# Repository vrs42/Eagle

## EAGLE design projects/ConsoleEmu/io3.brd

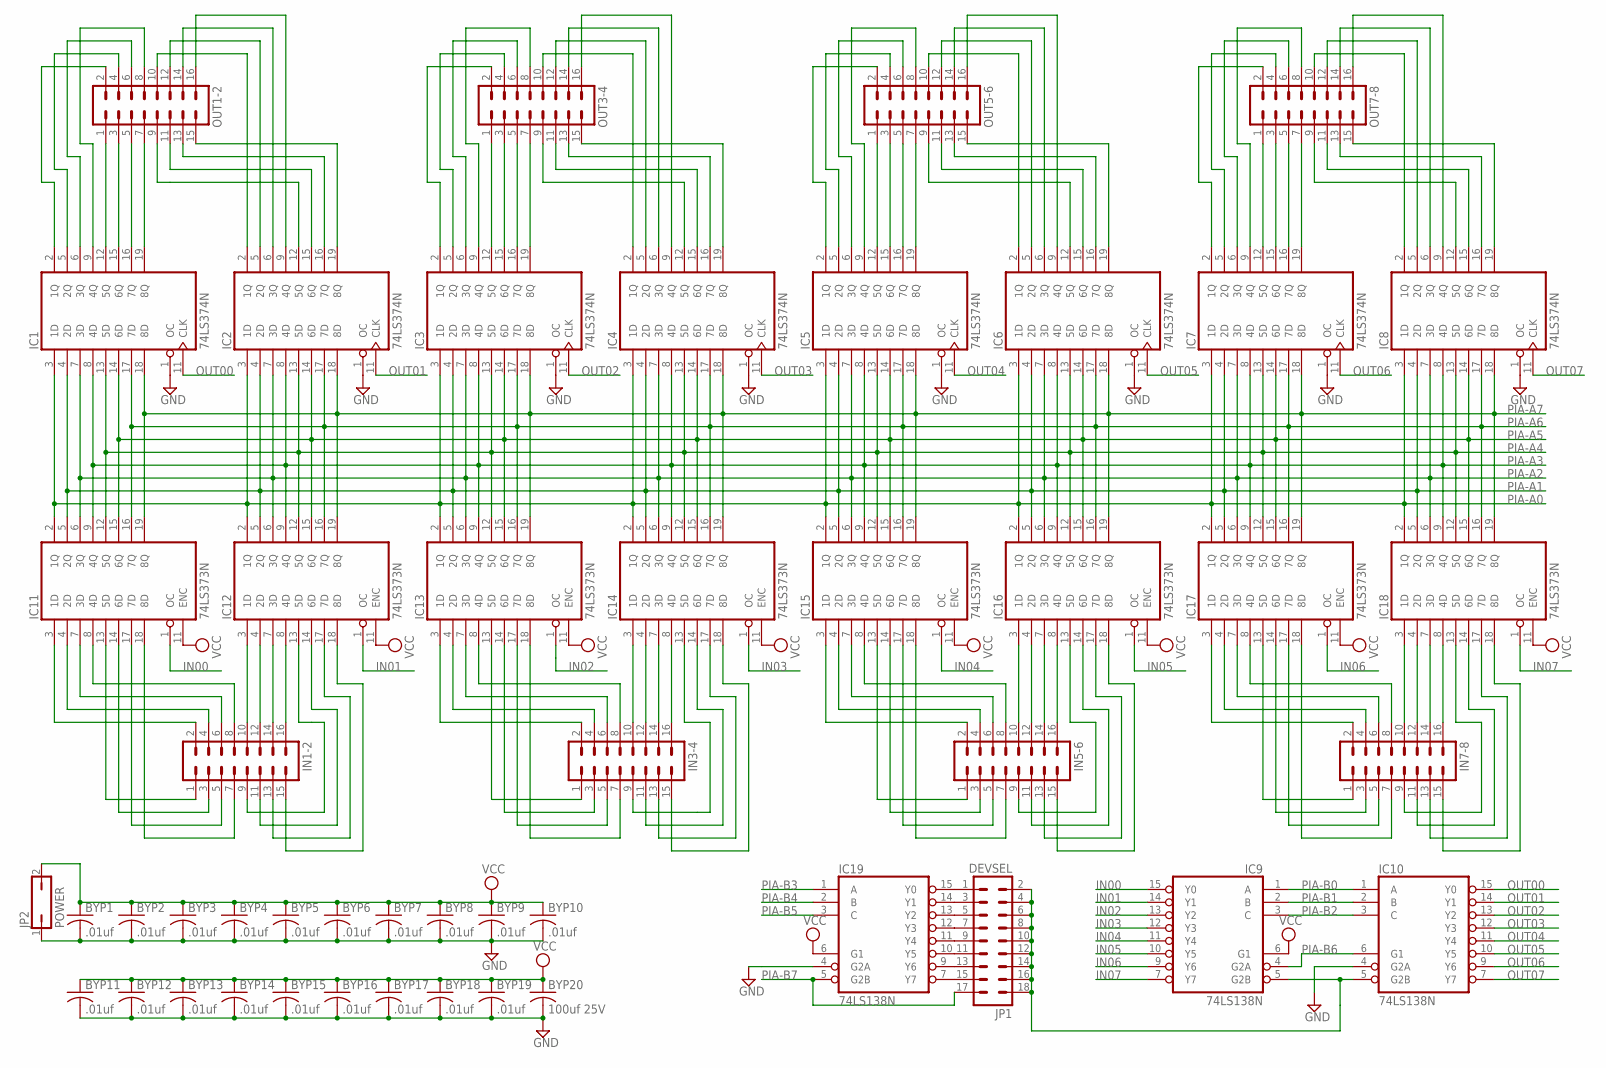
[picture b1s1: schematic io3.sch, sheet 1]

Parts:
BYP1, BYP2, BYP3, BYP4, BYP5, BYP6, BYP7, BYP8, BYP9, BYP10, BYP11, BYP12, BYP13, BYP14, BYP15, BYP16, BYP17, BYP18, BYP19: .01uf; C050-025X075
BYP20: 100uf 25V; C150-064X183
IC1, IC2, IC3, IC4, IC5, IC6, IC7, IC8: 74LS374N; DIL20
IC9, IC10, IC19: 74LS138N; DIL16
IC11, IC12, IC13, IC14, IC15, IC16, IC17, IC18: 74LS373N; DIL20
IN1-2, IN3-4, IN5-6, IN7-8: MA08-2
JP1: DEVSEL; MA09-2
JP2: POWER; JP1
OUT1-2, OUT3-4, OUT5-6, OUT7-8: MA08-2

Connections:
GND: BYP1.2, BYP2.2, BYP3.2, BYP4.2, BYP5.2, BYP6.2, BYP7.2, BYP8.2, BYP9.2, BYP10.2, BYP11.2, BYP12.2, BYP13.2, BYP14.2, BYP15.2, BYP16.2, BYP17.2, BYP18.2, BYP19.2, BYP20.2, IC1.1 (OC), IC1.10 (GND), IC2.1 (OC), IC2.10 (GND), IC3.1 (OC), IC3.10 (GND), IC4.1 (OC), IC4.10 (GND), IC5.1 (OC), IC5.10 (GND), IC6.1 (OC), IC6.10 (GND), IC7.1 (OC), IC7.10 (GND), IC8.1 (OC), IC8.10 (GND), IC9.8 (GND), IC10.4 (G2A), IC10.8 (GND), IC11.10 (GND), IC12.10 (GND), IC13.10 (GND), IC14.10 (GND), IC15.10 (GND), IC16.10 (GND), IC17.10 (GND), IC18.10 (GND), IC19.4 (G2A), IC19.8 (GND), JP2.1; also elsewhere on the board
IN00: IC9.15 (Y0), IC11.1 (OC)
IN01: IC9.14 (Y1), IC12.1 (OC)
IN02: IC9.13 (Y2), IC13.1 (OC)
IN03: IC9.12 (Y3), IC14.1 (OC)
IN04: IC9.11 (Y4), IC15.1 (OC)
IN05: IC9.10 (Y5), IC16.1 (OC)
IN06: IC9.9 (Y6), IC17.1 (OC)
IN07: IC9.7 (Y7), IC18.1 (OC)
unnamed: IC12.3 (1D), IN1-2.10
unnamed: IC12.4 (2D), IN1-2.12
unnamed: IC19.15 (Y0), JP1.1
unnamed: IC19.14 (Y1), JP1.3
unnamed: IC19.13 (Y2), JP1.5
unnamed: IC19.12 (Y3), JP1.7
unnamed: IC12.7 (3D), IN1-2.14
unnamed: IC12.8 (4D), IN1-2.16
unnamed: IC11.8 (4D), IN1-2.8
unnamed: IC11.7 (3D), IN1-2.6
unnamed: IC11.4 (2D), IN1-2.4
unnamed: IC11.3 (1D), IN1-2.2
unnamed: IC11.13 (5D), IN1-2.1
unnamed: IC11.14 (6D), IN1-2.3
unnamed: IC11.17 (7D), IN1-2.5
unnamed: IC11.18 (8D), IN1-2.7
unnamed: IC12.13 (5D), IN1-2.9
unnamed: IC12.14 (6D), IN1-2.11
unnamed: IC12.17 (7D), IN1-2.13
unnamed: IC12.18 (8D), IN1-2.15
unnamed: IC19.11 (Y4), JP1.9
unnamed: IC19.10 (Y5), JP1.11
unnamed: IC19.9 (Y6), JP1.13
unnamed: IC19.7 (Y7), JP1.15
unnamed: IC9.5 (G2B), IC10.5 (G2B), JP1.2, JP1.4, JP1.6, JP1.8, JP1.10, JP1.12, JP1.14, JP1.16, JP1.18
unnamed: IC5.2 (1Q), OUT5-6.2
unnamed: IC18.8 (4D), IN7-8.16
unnamed: IC18.3 (1D), IN7-8.10
unnamed: IC14.3 (1D), IN3-4.10
unnamed: IC14.4 (2D), IN3-4.12
unnamed: IC14.7 (3D), IN3-4.14
unnamed: IC14.8 (4D), IN3-4.16
unnamed: IC3.12 (5Q), OUT3-4.1
unnamed: IC3.15 (6Q), OUT3-4.3
unnamed: IC3.16 (7Q), OUT3-4.5
unnamed: IC3.19 (8Q), OUT3-4.7
unnamed: IC13.3 (1D), IN3-4.2
unnamed: IC13.4 (2D), IN3-4.4
unnamed: IC13.7 (3D), IN3-4.6
unnamed: IC13.8 (4D), IN3-4.8
unnamed: IC14.13 (5D), IN3-4.9
unnamed: IC14.14 (6D), IN3-4.11
unnamed: IC14.17 (7D), IN3-4.13
unnamed: IC14.18 (8D), IN3-4.15
unnamed: IC13.13 (5D), IN3-4.1
unnamed: IC13.14 (6D), IN3-4.3
unnamed: IC13.17 (7D), IN3-4.5
unnamed: IC13.18 (8D), IN3-4.7
unnamed: IC3.5 (2Q), OUT3-4.4
unnamed: IC3.6 (3Q), OUT3-4.6
unnamed: IC3.2 (1Q), OUT3-4.2
unnamed: IC3.9 (4Q), OUT3-4.8
unnamed: IC1.12 (5Q), OUT1-2.1
unnamed: IC1.15 (6Q), OUT1-2.3
unnamed: IC1.16 (7Q), OUT1-2.5
unnamed: IC1.19 (8Q), OUT1-2.7
unnamed: IC1.2 (1Q), OUT1-2.2
unnamed: IC1.5 (2Q), OUT1-2.4
unnamed: IC1.6 (3Q), OUT1-2.6
unnamed: IC1.9 (4Q), OUT1-2.8
unnamed: IC2.19 (8Q), OUT1-2.15
unnamed: IC2.16 (7Q), OUT1-2.13
unnamed: IC2.15 (6Q), OUT1-2.11
unnamed: IC2.12 (5Q), OUT1-2.9
unnamed: IC2.2 (1Q), OUT1-2.10
unnamed: IC2.5 (2Q), OUT1-2.12
unnamed: IC2.6 (3Q), OUT1-2.14
unnamed: IC2.9 (4Q), OUT1-2.16
unnamed: IC4.2 (1Q), OUT3-4.10
unnamed: IC4.5 (2Q), OUT3-4.12
unnamed: IC4.6 (3Q), OUT3-4.14
unnamed: IC4.9 (4Q), OUT3-4.16
unnamed: IC4.19 (8Q), OUT3-4.15
unnamed: IC4.16 (7Q), OUT3-4.13
unnamed: IC4.15 (6Q), OUT3-4.11
unnamed: IC4.12 (5Q), OUT3-4.9
unnamed: IC16.3 (1D), IN5-6.10
unnamed: IC16.4 (2D), IN5-6.12
unnamed: IC16.7 (3D), IN5-6.14
unnamed: IC16.8 (4D), IN5-6.16
unnamed: IC5.12 (5Q), OUT5-6.1
unnamed: IC5.15 (6Q), OUT5-6.3
unnamed: IC5.16 (7Q), OUT5-6.5
unnamed: IC5.19 (8Q), OUT5-6.7
unnamed: IC7.12 (5Q), OUT7-8.1
unnamed: IC7.15 (6Q), OUT7-8.3
unnamed: IC7.16 (7Q), OUT7-8.5
unnamed: IC7.19 (8Q), OUT7-8.7
unnamed: IC5.5 (2Q), OUT5-6.4
unnamed: IC5.6 (3Q), OUT5-6.6
unnamed: IC5.9 (4Q), OUT5-6.8
unnamed: IC6.12 (5Q), OUT5-6.9
unnamed: IC6.15 (6Q), OUT5-6.11
unnamed: IC18.4 (2D), IN7-8.12
unnamed: IC6.16 (7Q), OUT5-6.13
unnamed: IC6.19 (8Q), OUT5-6.15
unnamed: IC6.2 (1Q), OUT5-6.10
unnamed: IC6.5 (2Q), OUT5-6.12
unnamed: IC6.6 (3Q), OUT5-6.14
unnamed: IC6.9 (4Q), OUT5-6.16
unnamed: IC15.3 (1D), IN5-6.2
unnamed: IC15.4 (2D), IN5-6.4
unnamed: IC15.7 (3D), IN5-6.6
unnamed: IC15.8 (4D), IN5-6.8
unnamed: IC16.13 (5D), IN5-6.9
unnamed: IC16.14 (6D), IN5-6.11
unnamed: IC16.17 (7D), IN5-6.13
unnamed: IC16.18 (8D), IN5-6.15
unnamed: IC15.13 (5D), IN5-6.1
unnamed: IC15.14 (6D), IN5-6.3
unnamed: IC15.17 (7D), IN5-6.5
unnamed: IC15.18 (8D), IN5-6.7
unnamed: IC8.19 (8Q), OUT7-8.15
unnamed: IC8.16 (7Q), OUT7-8.13
unnamed: IC8.15 (6Q), OUT7-8.11
unnamed: IC8.12 (5Q), OUT7-8.9
unnamed: IC8.2 (1Q), OUT7-8.10
unnamed: IC8.5 (2Q), OUT7-8.12
unnamed: IC8.6 (3Q), OUT7-8.14
unnamed: IC8.9 (4Q), OUT7-8.16
unnamed: IC7.9 (4Q), OUT7-8.8
unnamed: IC7.6 (3Q), OUT7-8.6
unnamed: IC7.5 (2Q), OUT7-8.4
unnamed: IC18.7 (3D), IN7-8.14
unnamed: IC18.13 (5D), IN7-8.9
unnamed: IC18.14 (6D), IN7-8.11
unnamed: IC18.17 (7D), IN7-8.13
unnamed: IC18.18 (8D), IN7-8.15
unnamed: IC17.3 (1D), IN7-8.2
unnamed: IC17.4 (2D), IN7-8.4
unnamed: IC17.7 (3D), IN7-8.6
unnamed: IC17.8 (4D), IN7-8.8
unnamed: IC17.13 (5D), IN7-8.1
unnamed: IC17.14 (6D), IN7-8.3
unnamed: IC17.17 (7D), IN7-8.5
unnamed: IC17.18 (8D), IN7-8.7
unnamed: IC7.2 (1Q), OUT7-8.2
OUT00: IC1.11 (CLK), IC10.15 (Y0)
OUT01: IC2.11 (CLK), IC10.14 (Y1)
OUT02: IC3.11 (CLK), IC10.13 (Y2)
OUT03: IC4.11 (CLK), IC10.12 (Y3)
OUT04: IC5.11 (CLK), IC10.11 (Y4)
OUT05: IC6.11 (CLK), IC10.10 (Y5)
OUT06: IC7.11 (CLK), IC10.9 (Y6)
OUT07: IC8.11 (CLK), IC10.7 (Y7)
PIA-A0: IC1.3 (1D), IC2.3 (1D), IC3.3 (1D), IC4.3 (1D), IC5.3 (1D), IC6.3 (1D), IC7.3 (1D), IC8.3 (1D), IC11.2 (1Q), IC12.2 (1Q), IC13.2 (1Q), IC14.2 (1Q), IC15.2 (1Q), IC16.2 (1Q), IC17.2 (1Q), IC18.2 (1Q); also elsewhere on the board
PIA-A1: IC1.4 (2D), IC2.4 (2D), IC3.4 (2D), IC4.4 (2D), IC5.4 (2D), IC6.4 (2D), IC7.4 (2D), IC8.4 (2D), IC11.5 (2Q), IC12.5 (2Q), IC13.5 (2Q), IC14.5 (2Q), IC15.5 (2Q), IC16.5 (2Q), IC17.5 (2Q), IC18.5 (2Q); also elsewhere on the board
PIA-A2: IC1.7 (3D), IC2.7 (3D), IC3.7 (3D), IC4.7 (3D), IC5.7 (3D), IC6.7 (3D), IC7.7 (3D), IC8.7 (3D), IC11.6 (3Q), IC12.6 (3Q), IC13.6 (3Q), IC14.6 (3Q), IC15.6 (3Q), IC16.6 (3Q), IC17.6 (3Q), IC18.6 (3Q); also elsewhere on the board
PIA-A3: IC1.8 (4D), IC2.8 (4D), IC3.8 (4D), IC4.8 (4D), IC5.8 (4D), IC6.8 (4D), IC7.8 (4D), IC8.8 (4D), IC11.9 (4Q), IC12.9 (4Q), IC13.9 (4Q), IC14.9 (4Q), IC15.9 (4Q), IC16.9 (4Q), IC17.9 (4Q), IC18.9 (4Q); also elsewhere on the board
PIA-A4: IC1.13 (5D), IC2.13 (5D), IC3.13 (5D), IC4.13 (5D), IC5.13 (5D), IC6.13 (5D), IC7.13 (5D), IC8.13 (5D), IC11.12 (5Q), IC12.12 (5Q), IC13.12 (5Q), IC14.12 (5Q), IC15.12 (5Q), IC16.12 (5Q), IC17.12 (5Q), IC18.12 (5Q); also elsewhere on the board
PIA-A5: IC1.14 (6D), IC2.14 (6D), IC3.14 (6D), IC4.14 (6D), IC5.14 (6D), IC6.14 (6D), IC7.14 (6D), IC8.14 (6D), IC11.15 (6Q), IC12.15 (6Q), IC13.15 (6Q), IC14.15 (6Q), IC15.15 (6Q), IC16.15 (6Q), IC17.15 (6Q), IC18.15 (6Q); also elsewhere on the board
PIA-A6: IC1.17 (7D), IC2.17 (7D), IC3.17 (7D), IC4.17 (7D), IC5.17 (7D), IC6.17 (7D), IC7.17 (7D), IC8.17 (7D), IC11.16 (7Q), IC12.16 (7Q), IC13.16 (7Q), IC14.16 (7Q), IC15.16 (7Q), IC16.16 (7Q), IC17.16 (7Q), IC18.16 (7Q); also elsewhere on the board
PIA-A7: IC1.18 (8D), IC2.18 (8D), IC3.18 (8D), IC4.18 (8D), IC5.18 (8D), IC6.18 (8D), IC7.18 (8D), IC8.18 (8D), IC11.19 (8Q), IC12.19 (8Q), IC13.19 (8Q), IC14.19 (8Q), IC15.19 (8Q), IC16.19 (8Q), IC17.19 (8Q), IC18.19 (8Q); also elsewhere on the board
PIA-B0: IC9.1 (A), IC10.1 (A); also elsewhere on the board
PIA-B1: IC9.2 (B), IC10.2 (B); also elsewhere on the board
PIA-B2: IC9.3 (C), IC10.3 (C); also elsewhere on the board
PIA-B3: IC19.1 (A); also elsewhere on the board
PIA-B4: IC19.2 (B); also elsewhere on the board
PIA-B5: IC19.3 (C); also elsewhere on the board
PIA-B6: IC9.4 (G2A), IC10.6 (G1); also elsewhere on the board
PIA-B7: IC19.5 (G2B), JP1.17; also elsewhere on the board
VCC: BYP1.1, BYP2.1, BYP3.1, BYP4.1, BYP5.1, BYP6.1, BYP7.1, BYP8.1, BYP9.1, BYP10.1, BYP11.1, BYP12.1, BYP13.1, BYP14.1, BYP15.1, BYP16.1, BYP17.1, BYP18.1, BYP19.1, BYP20.1, IC1.20 (VCC), IC2.20 (VCC), IC3.20 (VCC), IC4.20 (VCC), IC5.20 (VCC), IC6.20 (VCC), IC7.20 (VCC), IC8.20 (VCC), IC9.6 (G1), IC9.16 (VCC), IC10.16 (VCC), IC11.11 (ENC), IC11.20 (VCC), IC12.11 (ENC), IC12.20 (VCC), IC13.11 (ENC), IC13.20 (VCC), IC14.11 (ENC), IC14.20 (VCC), IC15.11 (ENC), IC15.20 (VCC), IC16.11 (ENC), IC16.20 (VCC), IC17.11 (ENC), IC17.20 (VCC), IC18.11 (ENC), IC18.20 (VCC), IC19.6 (G1), IC19.16 (VCC), JP2.2; also elsewhere on the board

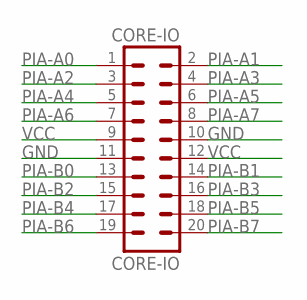
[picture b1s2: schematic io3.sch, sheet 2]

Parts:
CORE-IO: CORE-IO; MA10-2

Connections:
GND: CORE-IO.10, CORE-IO.11; also elsewhere on the board
PIA-A0: CORE-IO.1; also elsewhere on the board
PIA-A1: CORE-IO.2; also elsewhere on the board
PIA-A2: CORE-IO.3; also elsewhere on the board
PIA-A3: CORE-IO.4; also elsewhere on the board
PIA-A4: CORE-IO.5; also elsewhere on the board
PIA-A5: CORE-IO.6; also elsewhere on the board
PIA-A6: CORE-IO.7; also elsewhere on the board
PIA-A7: CORE-IO.8; also elsewhere on the board
PIA-B0: CORE-IO.13; also elsewhere on the board
PIA-B1: CORE-IO.14; also elsewhere on the board
PIA-B2: CORE-IO.15; also elsewhere on the board
PIA-B3: CORE-IO.16; also elsewhere on the board
PIA-B4: CORE-IO.17; also elsewhere on the board
PIA-B5: CORE-IO.18; also elsewhere on the board
PIA-B6: CORE-IO.19; also elsewhere on the board
PIA-B7: CORE-IO.20; also elsewhere on the board
VCC: CORE-IO.9, CORE-IO.12; also elsewhere on the board

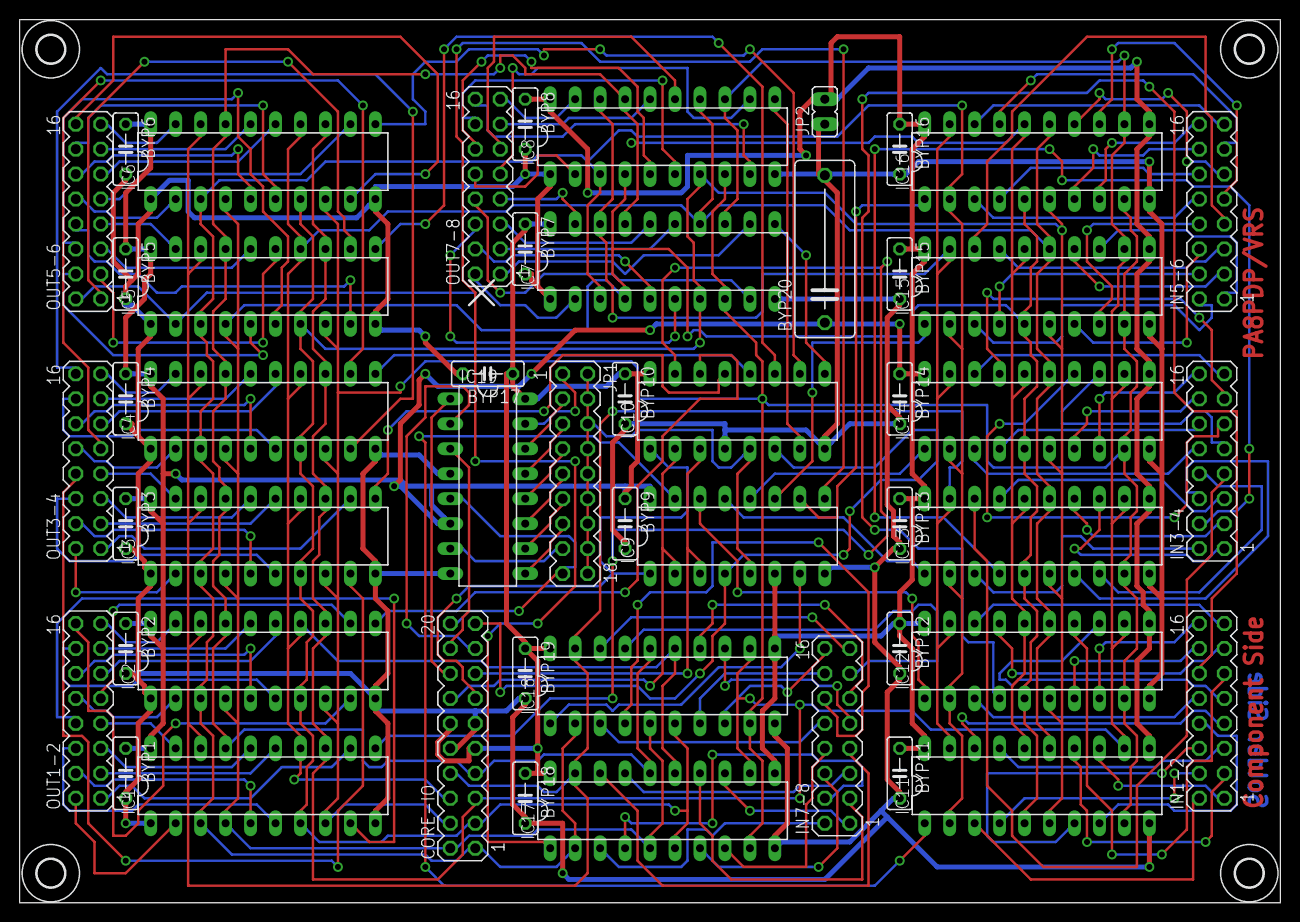
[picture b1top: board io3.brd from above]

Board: 2 copper layers, 128.2 x 89.8 mm, 54 parts (0 on the bottom side), 171 nets.

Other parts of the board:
U$1, U$2, U$3, U$4: 2,8

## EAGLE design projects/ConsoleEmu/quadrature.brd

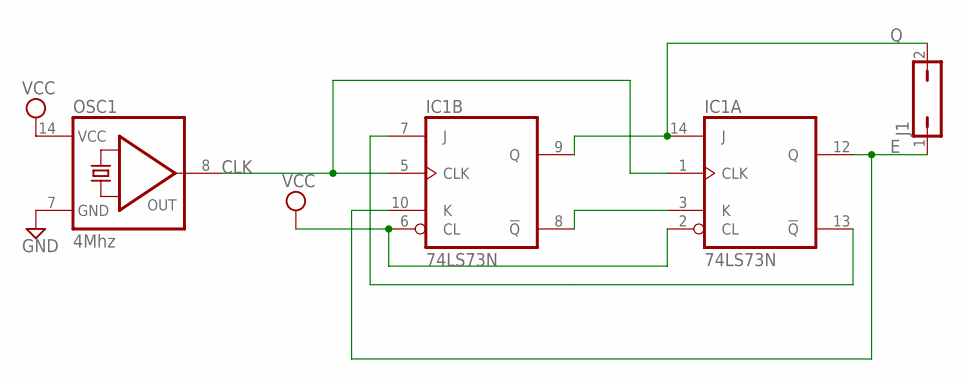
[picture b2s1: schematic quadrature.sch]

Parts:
IC1: 74LS73N; DIL14
J1: JP1Q; JP1
OSC1: 4Mhz; DIL14S

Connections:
CLK: IC1.1 (CLK), IC1.5 (CLK), OSC1.8 (OUT)
E: IC1.10 (K), IC1.12 (Q), J1.1
GND: IC1.11 (GND), OSC1.7 (GND)
unnamed: IC1.3 (K), IC1.8 (!Q)
unnamed: IC1.7 (J), IC1.13 (!Q)
Q: IC1.9 (Q), IC1.14 (J), J1.2
VCC: IC1.2 (CL), IC1.4 (VCC), IC1.6 (CL), OSC1.14 (VCC)

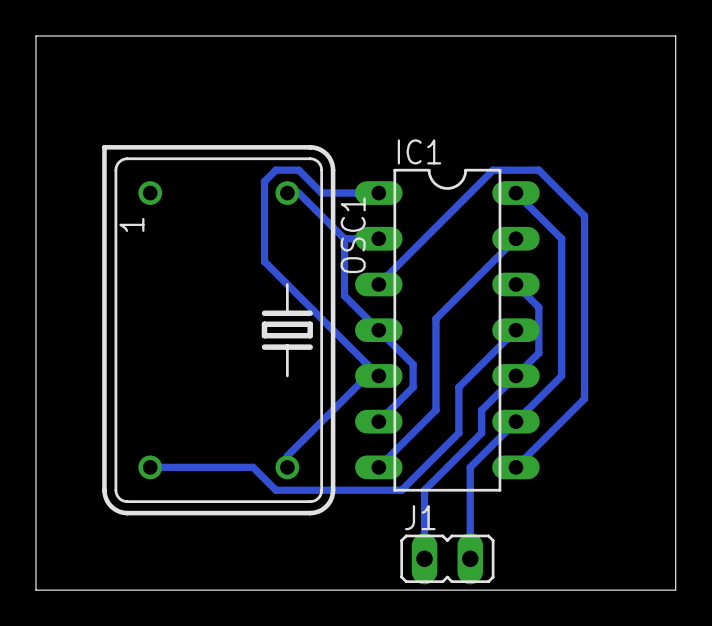
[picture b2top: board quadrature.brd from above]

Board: 2 copper layers, 35.5 x 30.8 mm, 3 parts (0 on the bottom side), 7 nets.

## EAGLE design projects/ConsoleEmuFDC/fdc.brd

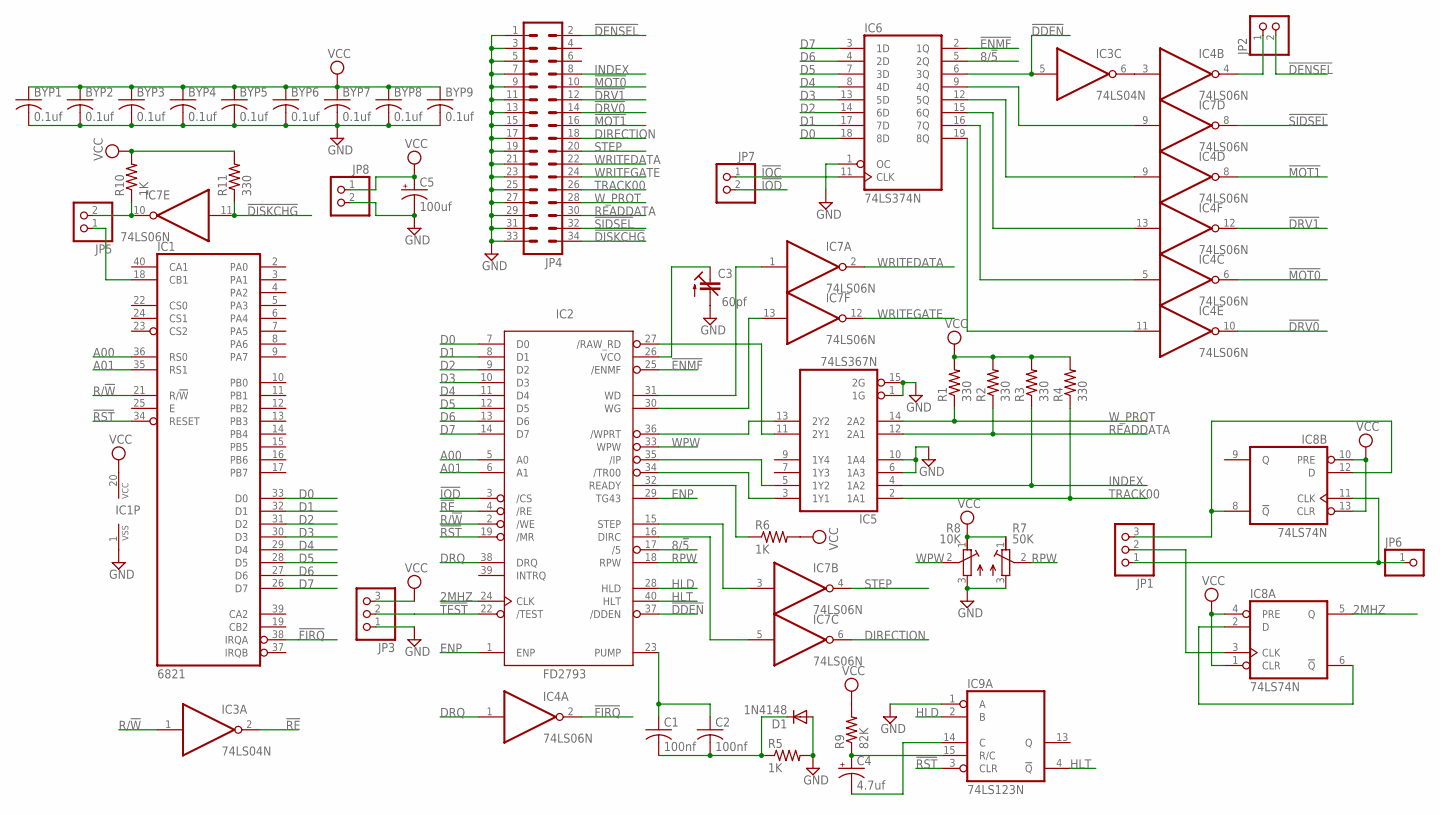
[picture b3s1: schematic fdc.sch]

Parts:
BYP1, BYP2, BYP3, BYP4, BYP5, BYP6, BYP7, BYP8, BYP9: 0.1uf; C050-025X075
C1, C2: 100nf; C050-025X075
C3: 60pf; CTRIM808-BC
C4: 4.7uf; E15-5
C5: 100uf; E15-5
D1: 1N4148; DO35-10
IC1: 6821; DIL40
IC2: FD2793; DIL40
IC3: 74LS04N; DIL14
IC4, IC7: 74LS06N; DIL14
IC5: 74LS367N; DIL16
IC6: 74LS374N; DIL20
IC8: 74LS74N; DIL14
IC9: 74LS123N; DIL16
JP1, JP3: PINHD-1X3; 1X03
JP2, JP5, JP7, JP8: PINHD-1X2; 1X02
JP4: MA17-2
JP6: PINHD-1X1; 1X01
R1, R2, R3, R4, R11: 330; 0207/10
R5, R6, R10: 1K; 0207/10
R7: 50K; RTRIM43P
R8: 10K; RTRIM43P
R9: 82K; 0207/10

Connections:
2MHZ: IC2.24 (CLK), IC8.5 (Q)
8/!5: IC2.17 (/5), IC6.5 (2Q)
!DDEN: IC2.37 (/DDEN), IC3.5 (I), IC6.6 (3Q)
!DENSEL: JP2.2, JP4.2
!DISKCHG: IC7.11 (I), JP4.34, R11.1
!DRV0: IC4.10 (O), JP4.14
!DRV1: IC4.12 (O), JP4.12
!ENMF: IC2.25 (/ENMF), IC6.2 (1Q)
!FIRQ: IC1.38 (IRQA), IC4.2 (O)
!IOC: IC6.11 (CLK), JP7.1
!IOD: IC2.3 (/CS), JP7.2
!MOT0: IC4.6 (O), JP4.10
!MOT1: IC4.8 (O), JP4.16
!RE: IC2.4 (/RE), IC3.2 (O)
!RST: IC1.34 (RESET), IC2.19 (/MR), IC9.3 (CLR)
!SIDSEL: IC7.8 (O), JP4.32
!TEST: IC2.22 (/TEST), JP3.2
A00: IC1.36 (RS0), IC2.5 (A0)
A01: IC1.35 (RS1), IC2.6 (A1)
CB1: IC1.18 (CB1), JP5.1
D0: IC1.33 (D0), IC2.7 (D0), IC6.18 (8D)
D1: IC1.32 (D1), IC2.8 (D1), IC6.17 (7D)
D2: IC1.31 (D2), IC2.9 (D2), IC6.14 (6D)
D3: IC1.30 (D3), IC2.10 (D3), IC6.13 (5D)
D4: IC1.29 (D4), IC2.11 (D4), IC6.8 (4D)
D5: IC1.28 (D5), IC2.12 (D5), IC6.7 (3D)
D6: IC1.27 (D6), IC2.13 (D6), IC6.4 (2D)
D7: IC1.26 (D7), IC2.14 (D7), IC6.3 (1D)
DIRECTION: IC7.6 (O), JP4.18
DRQ: IC2.38 (DRQ), IC4.1 (I)
ENP: IC2.1 (ENP), IC2.29 (TG43)
GND: BYP1.2, BYP2.2, BYP3.2, BYP4.2, BYP5.2, BYP6.2, BYP7.2, BYP8.2, BYP9.2, C3.2 (A), C5.-, D1.A, IC1.1 (VSS), IC2.20 (GND), IC3.7 (GND), IC4.7 (GND), IC5.1 (1G), IC5.6 (1A3), IC5.8 (GND), IC5.10 (1A4), IC5.15 (2G), IC6.1 (OC), IC6.10 (GND), IC7.7 (GND), IC8.7 (GND), IC9.1 (A), IC9.8 (GND), JP3.1, JP4.1, JP4.3, JP4.5, JP4.7, JP4.9, JP4.11, JP4.13, JP4.15, JP4.17, JP4.19, JP4.21, JP4.23, JP4.25, JP4.27, JP4.29, JP4.31, JP4.33, JP8.2, R5.2, R7.3 (A), R8.3 (A)
HLD: IC2.28 (HLD), IC9.2 (B)
HLT: IC2.40 (HLT), IC9.4 (!Q)
INDEX: IC5.4 (1A2), JP4.8, R3.1
unnamed: IC3.6 (O), IC4.3 (I)
unnamed: IC4.4 (O), JP2.1
unnamed: IC2.27 (/RAW_RD), IC5.11 (2Y1)
unnamed: IC4.11 (I), IC6.19 (8Q)
unnamed: IC4.5 (I), IC6.16 (7Q)
unnamed: IC4.13 (I), IC6.15 (6Q)
unnamed: IC4.9 (I), IC6.12 (5Q)
unnamed: C4.+, IC9.15 (R/C), R9.1
unnamed: C4.-, IC9.14 (C)
unnamed: IC2.32 (READY), R6.1
unnamed: IC6.9 (4Q), IC7.9 (I)
unnamed: IC2.16 (DIRC), IC7.5 (I)
unnamed: IC7.10 (O), JP5.2, R10.1
unnamed: IC2.34 (/TR00), IC5.3 (1Y1)
unnamed: IC2.35 (/IP), IC5.5 (1Y2)
unnamed: IC8.8 (!Q), IC8.12 (D), JP1.3
unnamed: IC2.36 (/WPRT), IC5.13 (2Y2)
unnamed: IC8.11 (CLK), JP1.1, JP6.1
unnamed: C3.1 (E), IC2.26 (VCO)
unnamed: C1.2, C2.2, D1.C, R5.1
unnamed: IC2.31 (WD), IC7.1 (I)
unnamed: IC2.30 (WG), IC7.13 (I)
unnamed: IC2.15 (STEP), IC7.3 (I)
unnamed: IC8.3 (CLK), JP1.2
unnamed: IC8.2 (D), IC8.6 (!Q)
PUMP: C1.1, C2.1, IC2.23 (PUMP)
R/!W: IC1.21 (R/!W), IC2.2 (/WE), IC3.1 (I)
READDATA: IC5.12 (2A1), JP4.30, R2.1
RPW: IC2.18 (RPW), R7.2 (S)
STEP: IC7.4 (O), JP4.20
TRACK00: IC5.2 (1A1), JP4.26, R4.1
VCC: BYP1.1, BYP2.1, BYP3.1, BYP4.1, BYP5.1, BYP6.1, BYP7.1, BYP8.1, BYP9.1, C5.+, IC1.20 (VCC), IC2.21 (VCC), IC3.14 (VCC), IC4.14 (VCC), IC5.16 (VCC), IC6.20 (VCC), IC7.14 (VCC), IC8.1 (CLR), IC8.4 (PRE), IC8.10 (PRE), IC8.13 (CLR), IC8.14 (VCC), IC9.16 (VCC), JP3.3, JP8.1, R1.2, R2.2, R3.2, R4.2, R6.2, R7.1 (E), R8.1 (E), R9.2, R10.2, R11.2
WPW: IC2.33 (WPW), R8.2 (S)
WRITEDATA: IC7.2 (O), JP4.22
WRITEGATE: IC7.12 (O), JP4.24
W_PROT: IC5.14 (2A2), JP4.28, R1.1

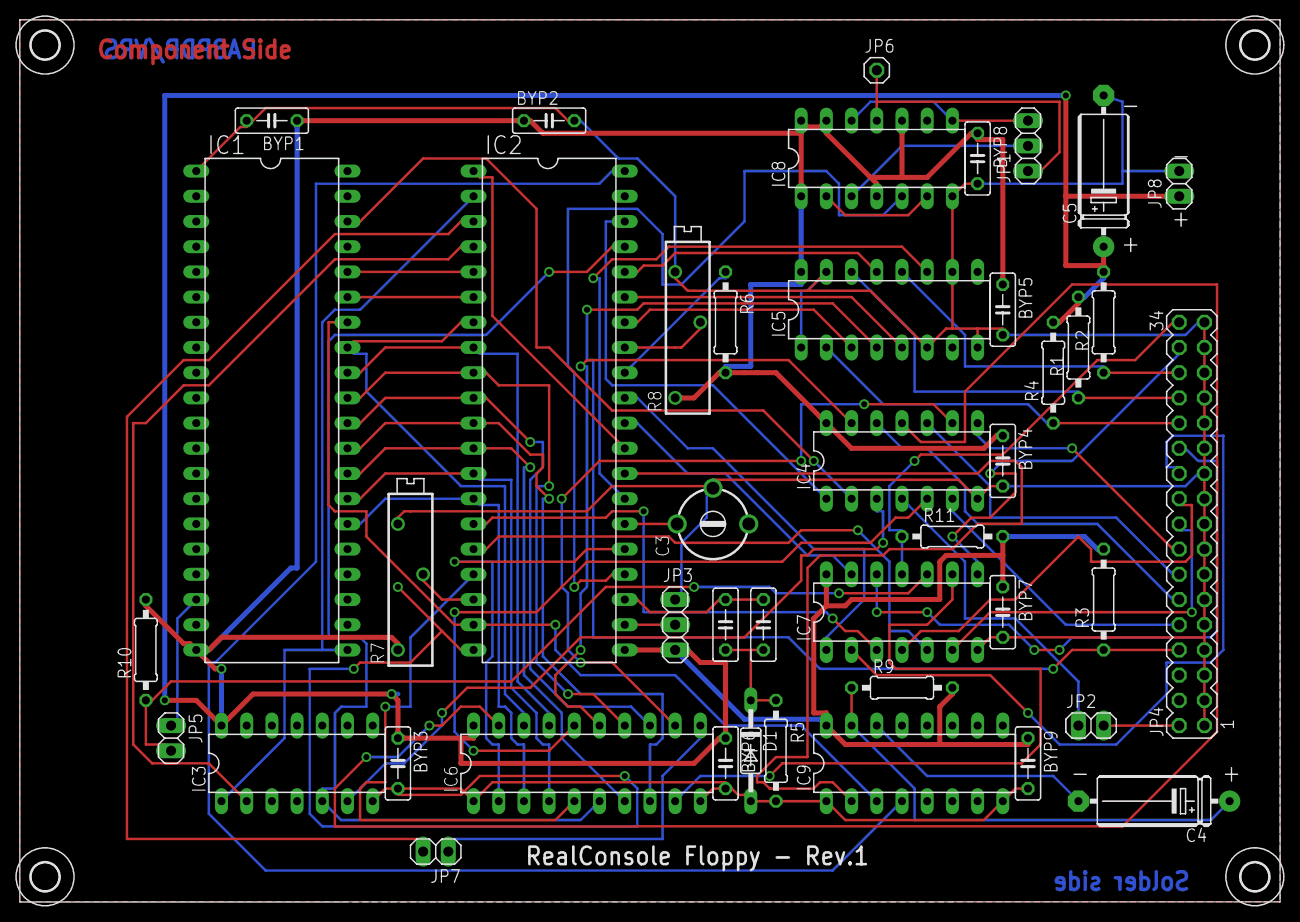
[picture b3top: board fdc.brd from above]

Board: 2 copper layers, 127.0 x 88.9 mm, 47 parts (0 on the bottom side), 71 nets.

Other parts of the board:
U$3, U$4, U$5, U$6: 2,8

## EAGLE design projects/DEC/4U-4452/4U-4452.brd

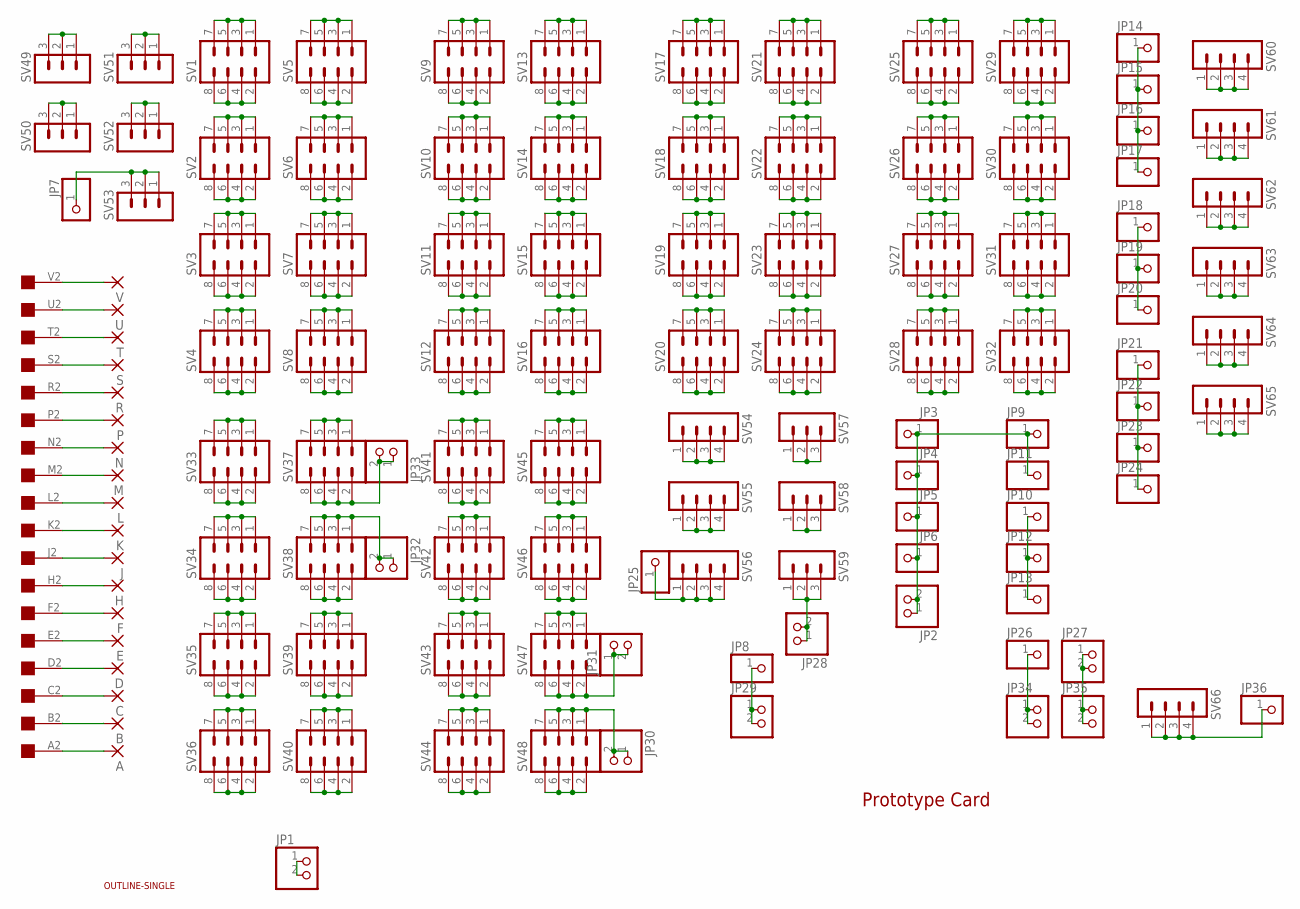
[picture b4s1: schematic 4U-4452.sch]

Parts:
A: 3,17/1,1
B: 3,17/1,1
C: 3,17/1,1
D: 3,17/1,1
E: 3,17/1,1
F: 3,17/1,1
H: 3,17/1,1
J: 3,17/1,1
JP1, JP2, JP27, JP28, JP29, JP30, JP31, JP32, JP33, JP34, JP35: PINHD-1X2; 1X02
JP3, JP4, JP5, JP6, JP7, JP8, JP9, JP10, JP11, JP12, JP13, JP14, JP15, JP16, JP17, JP18, JP19, JP20, JP21, JP22, JP23, JP24, JP25, JP26, JP36: PINHD-1X1; 1X01
K: 3,17/1,1
L: 3,17/1,1
M: 3,17/1,1
N: 3,17/1,1
P: 3,17/1,1
R: 3,17/1,1
S: 3,17/1,1
SV1, SV2, SV3, SV4, SV5, SV6, SV7, SV8, SV9, SV10, SV11, SV12, SV13, SV14, SV15, SV16, SV17, SV18, SV19, SV20, SV21, SV22, SV23, SV24, SV25, SV26, SV27, SV28, SV29, SV30, SV31, SV32, SV33, SV34, SV35, SV36, SV37, SV38, SV39, SV40, SV41, SV42, SV43, SV44, SV45, SV46, SV47, SV48: MA04-2
SV49, SV50, SV51, SV52, SV53, SV57, SV58, SV59: MA03-1
SV54, SV55, SV56, SV60, SV61, SV62, SV63, SV64, SV65, SV66: MA04-1
T: 3,17/1,1
U: 3,17/1,1
U$1: EDGE-1; EDGE-CON1
U$2: OUTLINE-SINGLE; SINGLE
V: 3,17/1,1

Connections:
A: A.1, U$1.A2
B: B.1, U$1.B2
D: D.1, U$1.D2
GND: C.1, U$1.C2
unnamed: U$1.V2, V.1
unnamed: U.1, U$1.U2
unnamed: T.1, U$1.T2
unnamed: S.1, U$1.S2
unnamed: R.1, U$1.R2
unnamed: P.1, U$1.P2
unnamed: N.1, U$1.N2
unnamed: M.1, U$1.M2
unnamed: L.1, U$1.L2
unnamed: K.1, U$1.K2
unnamed: J.1, U$1.J2
unnamed: H.1, U$1.H2
unnamed: F.1, U$1.F2
unnamed: E.1, U$1.E2
unnamed: SV1.1, SV1.3, SV1.5, SV1.7
unnamed: SV1.2, SV1.4, SV1.6, SV1.8
unnamed: SV2.1, SV2.3, SV2.5, SV2.7
unnamed: SV2.2, SV2.4, SV2.6, SV2.8
unnamed: SV3.1, SV3.3, SV3.5, SV3.7
unnamed: SV3.2, SV3.4, SV3.6, SV3.8
unnamed: SV4.1, SV4.3, SV4.5, SV4.7
unnamed: SV4.2, SV4.4, SV4.6, SV4.8
unnamed: SV5.1, SV5.3, SV5.5, SV5.7
unnamed: SV5.2, SV5.4, SV5.6, SV5.8
unnamed: SV6.1, SV6.3, SV6.5, SV6.7
unnamed: SV6.2, SV6.4, SV6.6, SV6.8
unnamed: SV7.1, SV7.3, SV7.5, SV7.7
unnamed: SV7.2, SV7.4, SV7.6, SV7.8
unnamed: SV8.1, SV8.3, SV8.5, SV8.7
unnamed: SV8.2, SV8.4, SV8.6, SV8.8
unnamed: SV9.1, SV9.3, SV9.5, SV9.7
unnamed: SV9.2, SV9.4, SV9.6, SV9.8
unnamed: SV10.1, SV10.3, SV10.5, SV10.7
unnamed: SV10.2, SV10.4, SV10.6, SV10.8
unnamed: SV11.1, SV11.3, SV11.5, SV11.7
unnamed: SV11.2, SV11.4, SV11.6, SV11.8
unnamed: SV12.1, SV12.3, SV12.5, SV12.7
unnamed: SV12.2, SV12.4, SV12.6, SV12.8
unnamed: SV13.1, SV13.3, SV13.5, SV13.7
unnamed: SV13.2, SV13.4, SV13.6, SV13.8
unnamed: SV14.1, SV14.3, SV14.5, SV14.7
unnamed: SV14.2, SV14.4, SV14.6, SV14.8
unnamed: SV15.1, SV15.3, SV15.5, SV15.7
unnamed: SV15.2, SV15.4, SV15.6, SV15.8
unnamed: SV16.1, SV16.3, SV16.5, SV16.7
unnamed: SV16.2, SV16.4, SV16.6, SV16.8
unnamed: SV17.1, SV17.3, SV17.5, SV17.7
unnamed: SV17.2, SV17.4, SV17.6, SV17.8
unnamed: SV18.1, SV18.3, SV18.5, SV18.7
unnamed: SV18.2, SV18.4, SV18.6, SV18.8
unnamed: SV19.1, SV19.3, SV19.5, SV19.7
unnamed: SV19.2, SV19.4, SV19.6, SV19.8
unnamed: SV20.1, SV20.3, SV20.5, SV20.7
unnamed: SV20.2, SV20.4, SV20.6, SV20.8
unnamed: SV21.1, SV21.3, SV21.5, SV21.7
unnamed: SV21.2, SV21.4, SV21.6, SV21.8
unnamed: SV22.1, SV22.3, SV22.5, SV22.7
unnamed: SV22.2, SV22.4, SV22.6, SV22.8
unnamed: SV23.1, SV23.3, SV23.5, SV23.7
unnamed: SV23.2, SV23.4, SV23.6, SV23.8
unnamed: SV24.1, SV24.3, SV24.5, SV24.7
unnamed: SV24.2, SV24.4, SV24.6, SV24.8
unnamed: SV25.1, SV25.3, SV25.5, SV25.7
unnamed: SV25.2, SV25.4, SV25.6, SV25.8
unnamed: SV26.1, SV26.3, SV26.5, SV26.7
unnamed: SV26.2, SV26.4, SV26.6, SV26.8
unnamed: SV27.1, SV27.3, SV27.5, SV27.7
unnamed: SV27.2, SV27.4, SV27.6, SV27.8
unnamed: SV28.1, SV28.3, SV28.5, SV28.7
unnamed: SV28.2, SV28.4, SV28.6, SV28.8
unnamed: SV29.1, SV29.3, SV29.5, SV29.7
unnamed: SV29.2, SV29.4, SV29.6, SV29.8
unnamed: SV30.1, SV30.3, SV30.5, SV30.7
unnamed: SV30.2, SV30.4, SV30.6, SV30.8
unnamed: SV31.1, SV31.3, SV31.5, SV31.7
unnamed: SV31.2, SV31.4, SV31.6, SV31.8
unnamed: SV32.1, SV32.3, SV32.5, SV32.7
unnamed: SV32.2, SV32.4, SV32.6, SV32.8
unnamed: SV33.1, SV33.3, SV33.5, SV33.7
unnamed: SV33.2, SV33.4, SV33.6, SV33.8
unnamed: SV34.1, SV34.3, SV34.5, SV34.7
unnamed: SV34.2, SV34.4, SV34.6, SV34.8
unnamed: SV35.1, SV35.3, SV35.5, SV35.7
unnamed: SV35.2, SV35.4, SV35.6, SV35.8
unnamed: SV36.1, SV36.3, SV36.5, SV36.7
unnamed: SV36.2, SV36.4, SV36.6, SV36.8
unnamed: SV37.1, SV37.3, SV37.5, SV37.7
unnamed: JP33.1, JP33.2, SV37.2, SV37.4, SV37.6, SV37.8
unnamed: JP32.1, JP32.2, SV38.1, SV38.3, SV38.5, SV38.7
unnamed: SV38.2, SV38.4, SV38.6, SV38.8
unnamed: SV39.1, SV39.3, SV39.5, SV39.7
unnamed: SV39.2, SV39.4, SV39.6, SV39.8
unnamed: SV40.1, SV40.3, SV40.5, SV40.7
unnamed: SV40.2, SV40.4, SV40.6, SV40.8
unnamed: SV41.1, SV41.3, SV41.5, SV41.7
unnamed: SV41.2, SV41.4, SV41.6, SV41.8
unnamed: SV42.1, SV42.3, SV42.5, SV42.7
unnamed: SV42.2, SV42.4, SV42.6, SV42.8
unnamed: SV43.1, SV43.3, SV43.5, SV43.7
unnamed: SV43.2, SV43.4, SV43.6, SV43.8
unnamed: SV44.1, SV44.3, SV44.5, SV44.7
unnamed: SV44.2, SV44.4, SV44.6, SV44.8
unnamed: SV45.1, SV45.3, SV45.5, SV45.7
unnamed: SV45.2, SV45.4, SV45.6, SV45.8
unnamed: SV46.1, SV46.3, SV46.5, SV46.7
unnamed: SV46.2, SV46.4, SV46.6, SV46.8
unnamed: SV47.1, SV47.3, SV47.5, SV47.7
unnamed: JP31.1, JP31.2, SV47.2, SV47.4, SV47.6, SV47.8
unnamed: JP30.1, JP30.2, SV48.1, SV48.3, SV48.5, SV48.7
unnamed: JP10.1, JP12.1, JP13.1
unnamed: SV51.1, SV51.2, SV51.3
unnamed: SV50.1, SV50.2, SV50.3
unnamed: SV49.1, SV49.2, SV49.3
unnamed: SV52.1, SV52.2, SV52.3
unnamed: JP7.1, SV53.1, SV53.2, SV53.3
unnamed: JP1.1, JP1.2
unnamed: JP2.1, JP2.2, JP3.1, JP4.1, JP5.1, JP6.1, JP9.1, JP11.1
unnamed: SV54.1, SV54.2, SV54.3, SV54.4
unnamed: SV55.1, SV55.2, SV55.3, SV55.4
unnamed: JP25.1, SV56.1, SV56.2, SV56.3, SV56.4
unnamed: SV58.1, SV58.2, SV58.3
unnamed: SV57.1, SV57.2, SV57.3
unnamed: JP28.1, JP28.2, SV59.1, SV59.2, SV59.3
unnamed: JP21.1, JP22.1, JP23.1, JP24.1
unnamed: JP18.1, JP19.1, JP20.1
unnamed: JP14.1, JP15.1, JP16.1, JP17.1
unnamed: SV60.1, SV60.2, SV60.3, SV60.4
unnamed: SV61.1, SV61.2, SV61.3, SV61.4
unnamed: SV62.1, SV62.2, SV62.3, SV62.4
unnamed: SV63.1, SV63.2, SV63.3, SV63.4
unnamed: SV64.1, SV64.2, SV64.3, SV64.4
unnamed: SV65.1, SV65.2, SV65.3, SV65.4
unnamed: JP27.1, JP27.2, JP35.1, JP35.2
unnamed: SV48.2, SV48.4, SV48.6, SV48.8
unnamed: JP8.1, JP29.1, JP29.2
unnamed: JP26.1, JP34.1, JP34.2
unnamed: JP36.1, SV66.1, SV66.2, SV66.3, SV66.4

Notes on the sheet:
Prototype Card

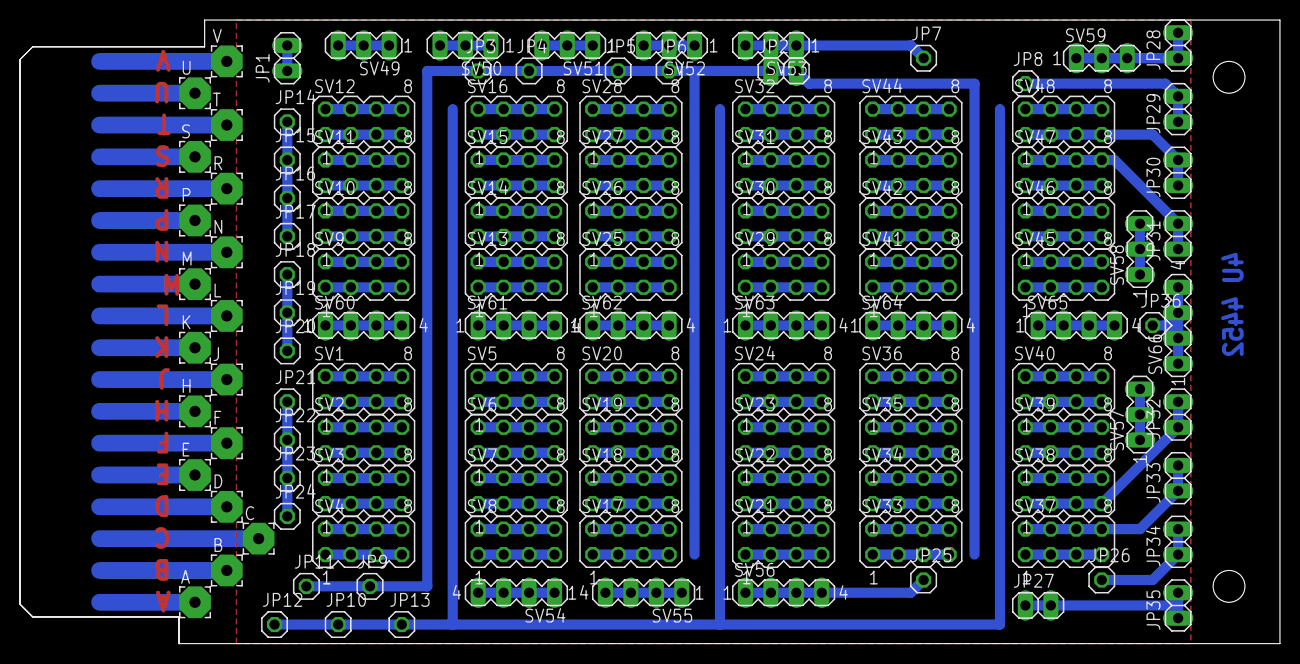
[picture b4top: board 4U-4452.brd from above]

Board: 2 copper layers, 125.7 x 62.2 mm, 122 parts (0 on the bottom side), 141 nets.
